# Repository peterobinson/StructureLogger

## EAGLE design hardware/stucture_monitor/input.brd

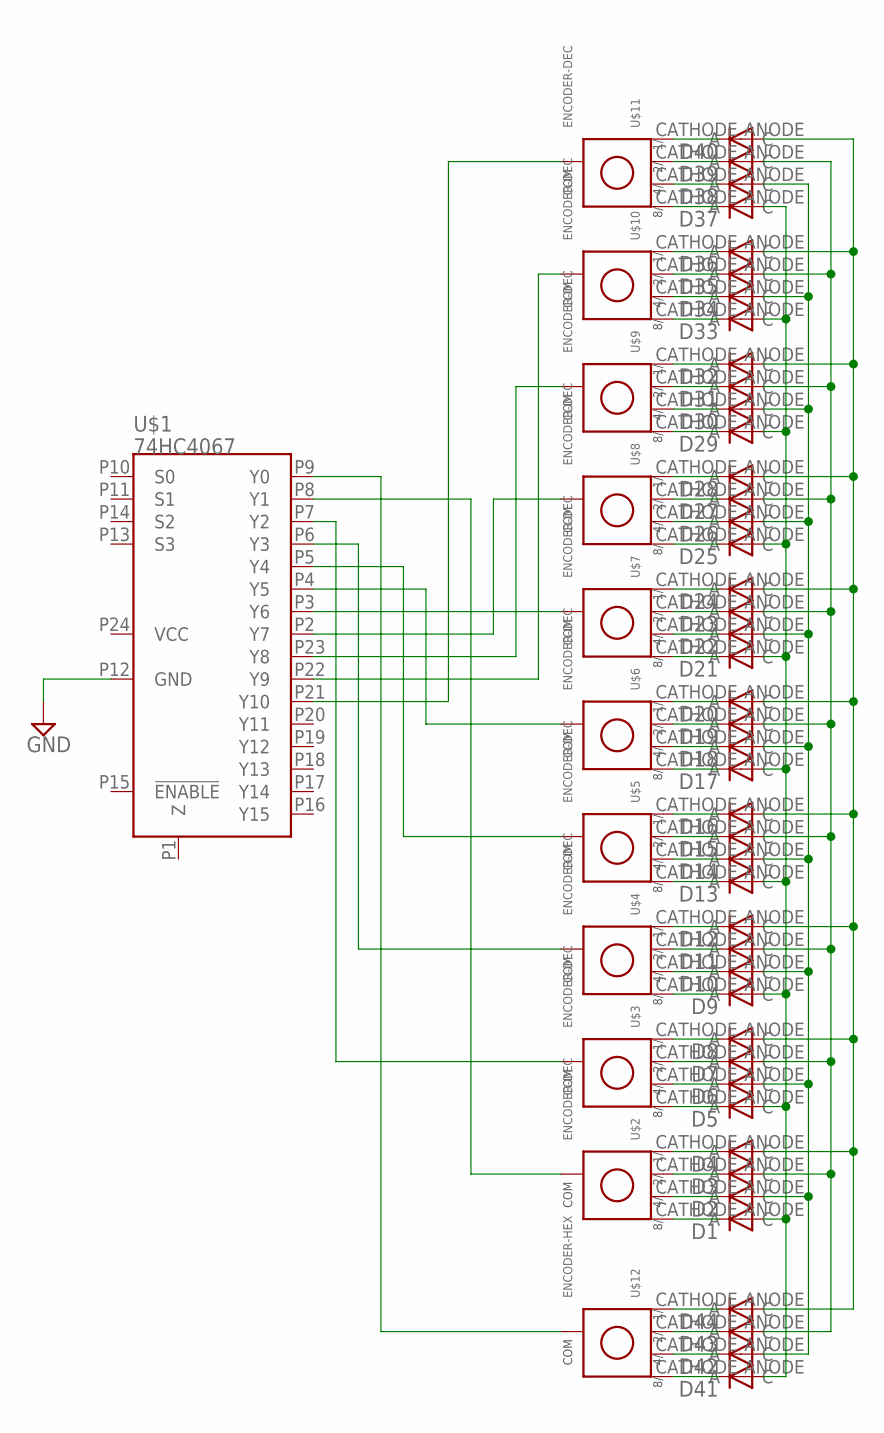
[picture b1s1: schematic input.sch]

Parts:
D1, D2, D3, D4, D5, D6, D7, D8, D9, D10, D11, D12, D13, D14, D15, D16, D17, D18, D19, D20, D21, D22, D23, D24, D25, D26, D27, D28, D29, D30, D31, D32, D33, D34, D35, D36, D37, D38, D39, D40, D41, D42, D43, D44: TS4148; 0805
U$1: 74HC4067; DIP-24
U$2, U$3, U$4, U$5, U$6, U$7, U$8, U$9, U$10, U$11: ENCODER-DEC; 4-BIT-ENCODER
U$12: ENCODER-HEX; 4-BIT-ENCODER

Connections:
GND: U$1.P12 (GND)
unnamed: D1.CATHODE (C), U$2.8/
unnamed: D2.CATHODE (C), U$2.4/
unnamed: D3.CATHODE (C), U$2.2/
unnamed: D4.CATHODE (C), U$2.1/
unnamed: D5.CATHODE (C), U$3.8/
unnamed: D6.CATHODE (C), U$3.4/
unnamed: D7.CATHODE (C), U$3.2/
unnamed: D8.CATHODE (C), U$3.1/
unnamed: D9.CATHODE (C), U$4.8/
unnamed: D10.CATHODE (C), U$4.4/
unnamed: D11.CATHODE (C), U$4.2/
unnamed: D12.CATHODE (C), U$4.1/
unnamed: D13.CATHODE (C), U$5.8/
unnamed: D14.CATHODE (C), U$5.4/
unnamed: D15.CATHODE (C), U$5.2/
unnamed: D16.CATHODE (C), U$5.1/
unnamed: D17.CATHODE (C), U$6.8/
unnamed: D18.CATHODE (C), U$6.4/
unnamed: D19.CATHODE (C), U$6.2/
unnamed: D20.CATHODE (C), U$6.1/
unnamed: D21.CATHODE (C), U$7.8/
unnamed: D22.CATHODE (C), U$7.4/
unnamed: D23.CATHODE (C), U$7.2/
unnamed: D24.CATHODE (C), U$7.1/
unnamed: D25.CATHODE (C), U$8.8/
unnamed: D26.CATHODE (C), U$8.4/
unnamed: D27.CATHODE (C), U$8.2/
unnamed: D28.CATHODE (C), U$8.1/
unnamed: D29.CATHODE (C), U$9.8/
unnamed: D30.CATHODE (C), U$9.4/
unnamed: D31.CATHODE (C), U$9.2/
unnamed: D32.CATHODE (C), U$9.1/
unnamed: D33.CATHODE (C), U$10.8/
unnamed: D34.CATHODE (C), U$10.4/
unnamed: D35.CATHODE (C), U$10.2/
unnamed: D36.CATHODE (C), U$10.1/
unnamed: D37.CATHODE (C), U$11.8/
unnamed: D38.CATHODE (C), U$11.4/
unnamed: D39.CATHODE (C), U$11.2/
unnamed: D40.CATHODE (C), U$11.1/
unnamed: D41.CATHODE (C), U$12.8/
unnamed: D42.CATHODE (C), U$12.4/
unnamed: D43.CATHODE (C), U$12.2/
unnamed: D44.CATHODE (C), U$12.1/
unnamed: D1.ANODE (A), D5.ANODE (A), D9.ANODE (A), D13.ANODE (A), D17.ANODE (A), D21.ANODE (A), D25.ANODE (A), D29.ANODE (A), D33.ANODE (A), D37.ANODE (A), D41.ANODE (A)
unnamed: D2.ANODE (A), D6.ANODE (A), D10.ANODE (A), D14.ANODE (A), D18.ANODE (A), D22.ANODE (A), D26.ANODE (A), D30.ANODE (A), D34.ANODE (A), D38.ANODE (A), D42.ANODE (A)
unnamed: D3.ANODE (A), D7.ANODE (A), D11.ANODE (A), D15.ANODE (A), D19.ANODE (A), D23.ANODE (A), D27.ANODE (A), D31.ANODE (A), D35.ANODE (A), D39.ANODE (A), D43.ANODE (A)
unnamed: D4.ANODE (A), D8.ANODE (A), D12.ANODE (A), D16.ANODE (A), D20.ANODE (A), D24.ANODE (A), D28.ANODE (A), D32.ANODE (A), D36.ANODE (A), D40.ANODE (A), D44.ANODE (A)
unnamed: U$1.P8 (Y1), U$2.COMMON
unnamed: U$1.P7 (Y2), U$3.COMMON
unnamed: U$1.P6 (Y3), U$4.COMMON
unnamed: U$1.P4 (Y5), U$6.COMMON
unnamed: U$1.P3 (Y6), U$7.COMMON
unnamed: U$1.P2 (Y7), U$8.COMMON
unnamed: U$1.P9 (Y0), U$12.COMMON
unnamed: U$1.P23 (Y8), U$9.COMMON
unnamed: U$1.P22 (Y9), U$10.COMMON
unnamed: U$1.P5 (Y4), U$5.COMMON
unnamed: U$1.P21 (Y10), U$11.COMMON
VCC: U$1.P24 (VCC)

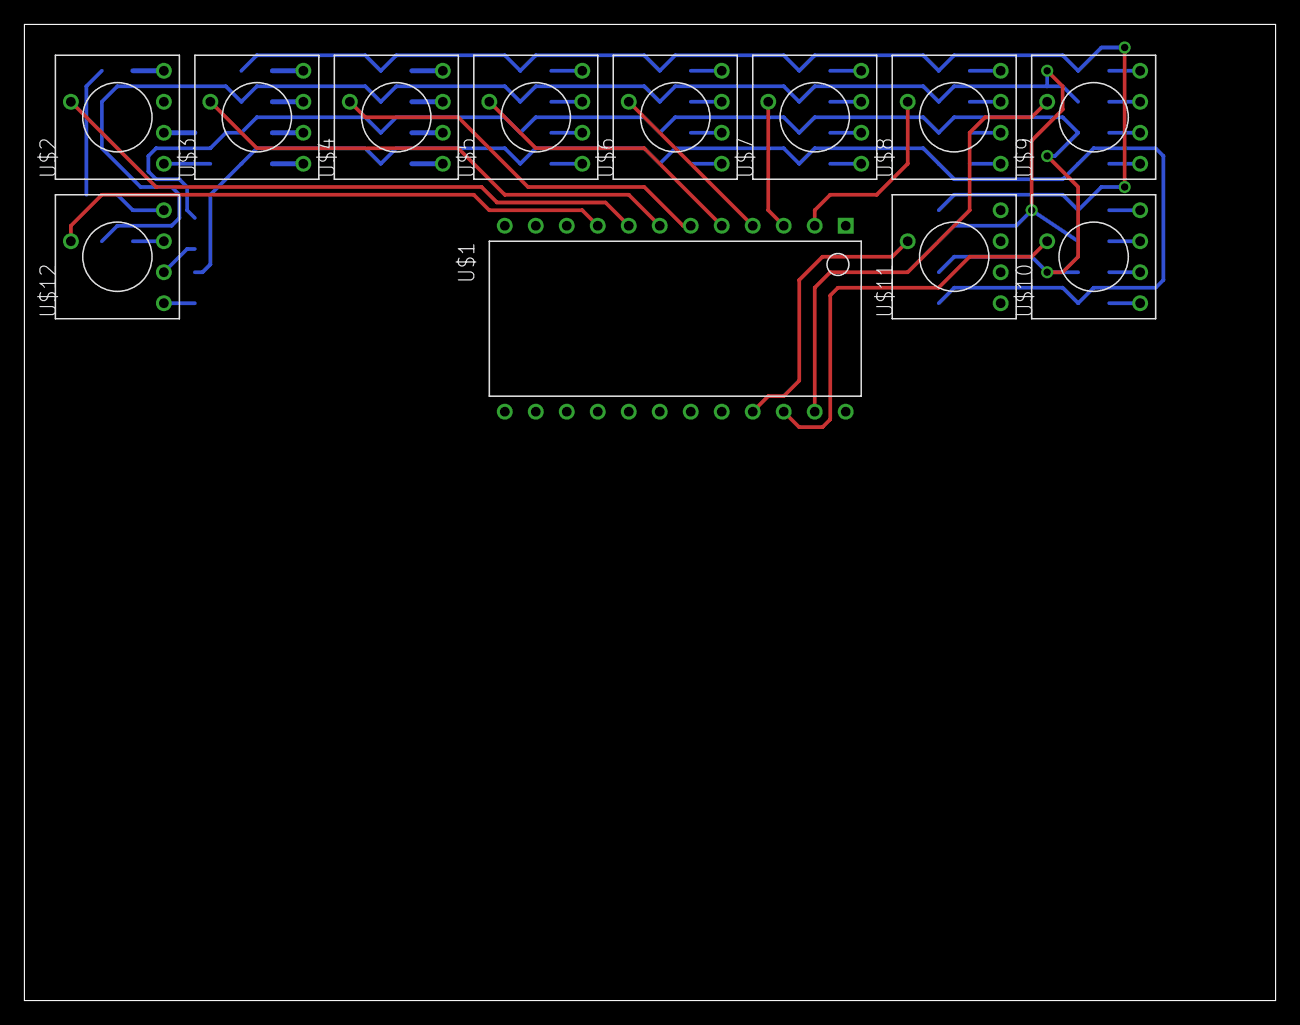
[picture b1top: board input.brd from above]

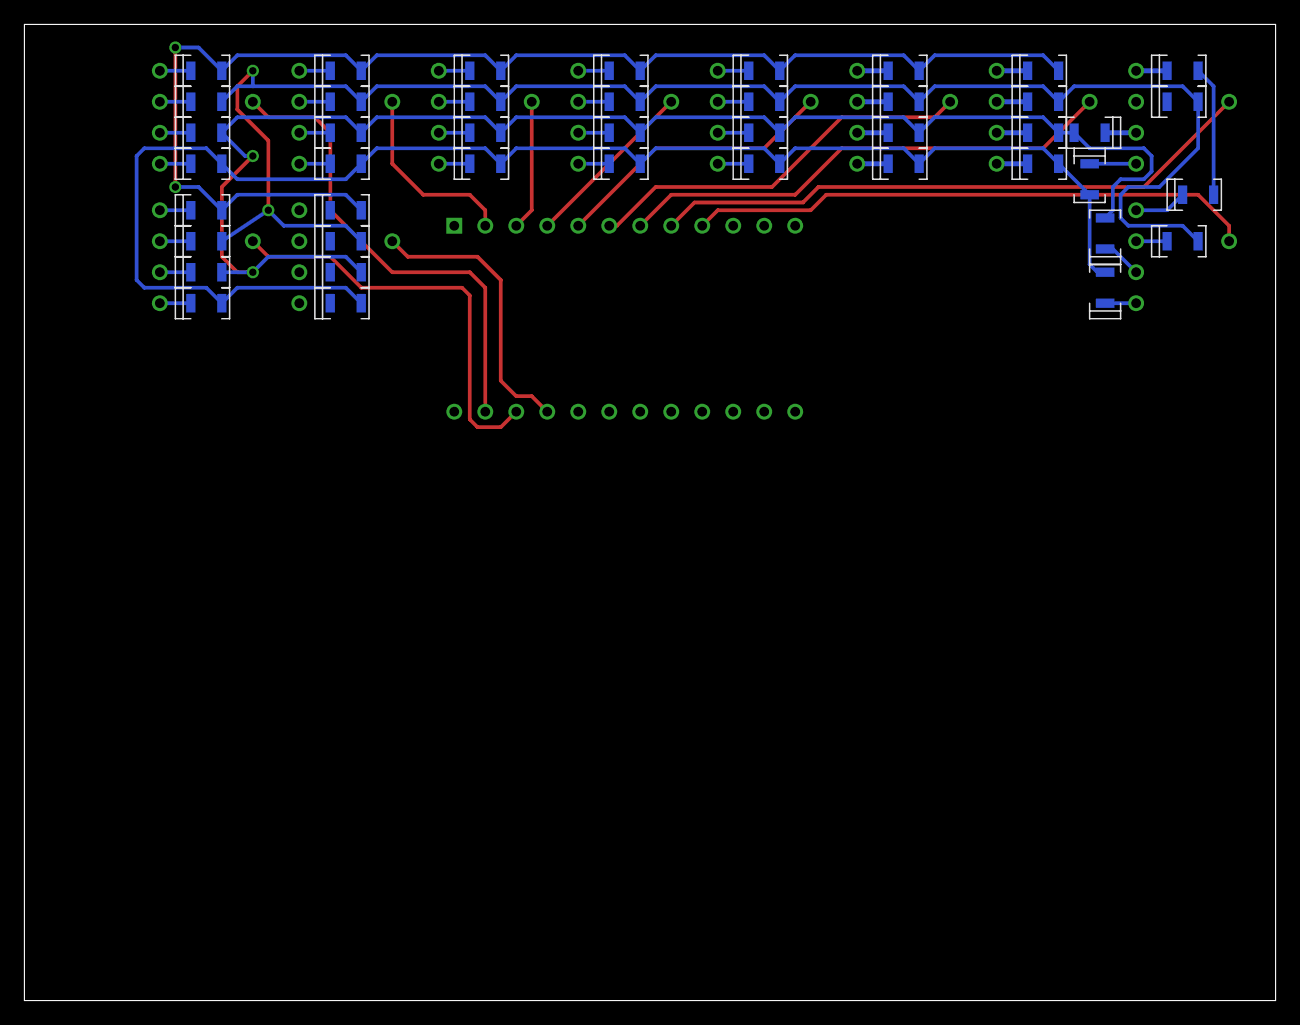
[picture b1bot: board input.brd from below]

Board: 2 copper layers, 102.5 x 80.0 mm, 56 parts (44 on the bottom side), 59 nets.

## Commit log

2013-06-09 Initial commit for project
2013-06-09 Software added
2013-06-09 Sending SMS working
2013-06-11 begun work on library for sim900
2013-06-12 Improved SIM900 lib with result parsing
2013-06-13 Created SMS sending function (untested)
2013-06-14 now sends sms's correctly
    Key was to wait for the modem to respond with "> " before sending the
    message
2013-06-15 Fast SMS sending complete
2013-06-15 Started work on retrieving NTP time
    Currently able to send UDP packet using terminal. Currently working out
    algorithm to calculate date from the unix timestamp that is returned.
2013-06-17 started writing NTP UTC decoding
    don't know if it works yet!
2013-06-19 NTP time to parts algorithm working
2013-06-20 drafted connect function (untested)
2013-07-30 further tinkering with the GPRS connection function
2013-08-11 Fetch UTC and decode working
    Issue was with the packet created by ntp.c getting corrupted before it
    was outputted.
2013-08-18 Modified ntp packet creation use defined buffer
2013-08-21 Replaced delays with proper polling for bytes
